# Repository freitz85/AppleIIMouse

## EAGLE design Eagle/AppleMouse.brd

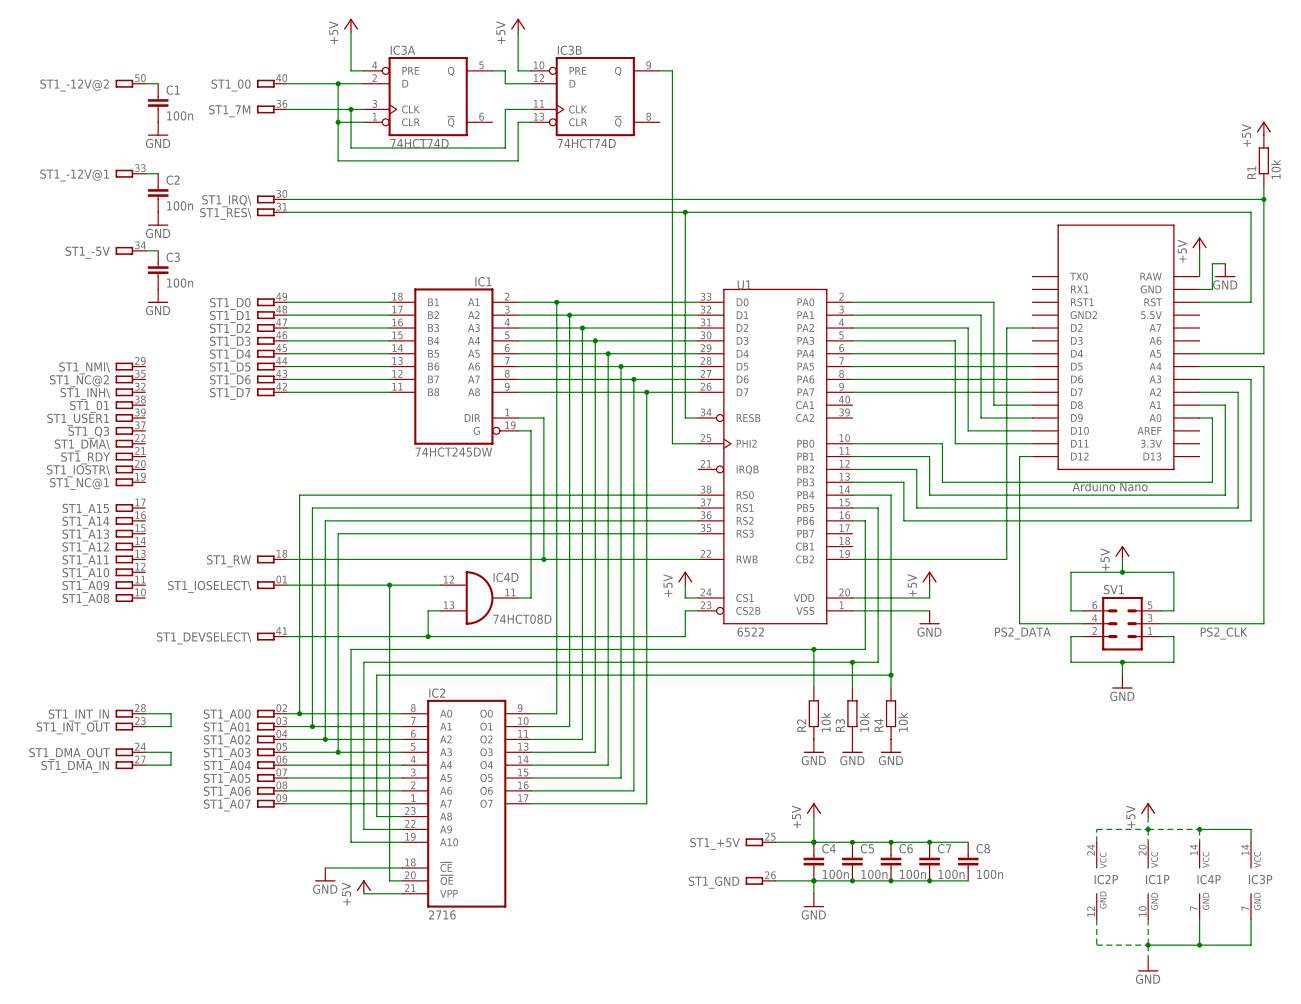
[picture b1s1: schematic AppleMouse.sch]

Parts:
C1, C2, C3, C4, C5, C6, C7, C8: 100n; C0805
IC1: 74HCT245DW; SO20W
IC2: 2716; DIL24
IC3: 74HCT74D; SO14
IC4: 74HCT08D; SO14
R1, R2, R3, R4: 10k; R0805
ST1: A2-50PINSLOT1-3; A2-50PIN-SL1-3
SV1: ML6
U1: 6522; DIP40
U$1: NANO

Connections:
+5V: C4.1, C5.1, C6.1, C7.1, C8.1, IC1.20 (VCC), IC2.21 (VPP), IC2.24 (VCC), IC3.4 (PRE), IC3.10 (PRE), IC3.14 (VCC), IC4.14 (VCC), R1.2, ST1.25, SV1.5, SV1.6, U1.20 (VDD), U1.24 (CS1), U$1.RAW
GND: C1.2, C2.2, C3.2, C4.2, C5.2, C6.2, C7.2, C8.2, IC1.10 (GND), IC2.12 (GND), IC2.18 (!CE), IC3.7 (GND), IC4.7 (GND), R2.1, R3.1, R4.1, ST1.26, SV1.1, SV1.2, U1.1 (VSS), U$1.GND
unnamed: IC1.18 (B1), ST1.49
unnamed: IC1.17 (B2), ST1.48
unnamed: IC1.16 (B3), ST1.47
unnamed: IC1.15 (B4), ST1.46
unnamed: IC1.14 (B5), ST1.45
unnamed: IC1.13 (B6), ST1.44
unnamed: IC1.12 (B7), ST1.43
unnamed: IC1.11 (B8), ST1.42
unnamed: IC1.5 (A4), IC2.13 (O3), U1.30 (D3)
unnamed: IC1.4 (A3), IC2.11 (O2), U1.31 (D2)
unnamed: IC1.3 (A2), IC2.10 (O1), U1.32 (D1)
unnamed: IC1.2 (A1), IC2.9 (O0), U1.33 (D0)
unnamed: IC1.9 (A8), IC2.17 (O7), U1.26 (D7)
unnamed: IC1.7 (A6), IC2.15 (O5), U1.28 (D5)
unnamed: IC1.8 (A7), IC2.16 (O6), U1.27 (D6)
unnamed: R1.1, ST1.30, U$1.A5
unnamed: ST1.31, U1.34 (RESB), U$1.RST
unnamed: U1.13 (PB3), U$1.A3
unnamed: IC2.20 (!OE), IC4.12 (I0), ST1.01
unnamed: U1.10 (PB0), U$1.A0
unnamed: IC2.7 (A1), ST1.03, U1.37 (RS1)
unnamed: U1.12 (PB2), U$1.A2
unnamed: IC2.5 (A3), ST1.05, U1.35 (RS3)
unnamed: IC2.4 (A4), ST1.06
unnamed: IC2.3 (A5), ST1.07
unnamed: IC2.2 (A6), ST1.08
unnamed: IC2.1 (A7), ST1.09
unnamed: IC1.1 (DIR), ST1.18, U1.22 (RWB)
unnamed: C1.1, ST1.50
unnamed: C2.1, ST1.33
unnamed: ST1.24, ST1.27
unnamed: ST1.23, ST1.28
unnamed: C3.1, ST1.34
unnamed: U1.19 (CB2), U$1.D2
unnamed: IC2.8 (A0), ST1.02, U1.38 (RS0)
unnamed: U1.11 (PB1), U$1.A1
unnamed: IC4.13 (I1), ST1.41, U1.23 (CS2B)
unnamed: IC2.6 (A2), ST1.04, U1.36 (RS2)
unnamed: IC1.6 (A5), IC2.14 (O4), U1.29 (D4)
unnamed: U1.3 (PA1), U$1.D9
unnamed: U1.2 (PA0), U$1.D8
unnamed: U1.4 (PA2), U$1.D10
unnamed: U1.5 (PA3), U$1.D11
unnamed: U1.6 (PA4), U$1.D4
unnamed: U1.7 (PA5), U$1.D5
unnamed: U1.8 (PA6), U$1.D6
unnamed: U1.9 (PA7), U$1.D7
unnamed: IC3.9 (Q), U1.25 (PHI2)
unnamed: IC2.23 (A8), R4.2, U1.14 (PB4)
unnamed: IC2.22 (A9), R3.2, U1.15 (PB5)
unnamed: IC2.19 (A10), R2.2, U1.16 (PB6)
unnamed: IC1.19 (G), IC4.11 (O)
unnamed: IC3.5 (Q), IC3.12 (D)
unnamed: IC3.1 (CLR), IC3.2 (D), IC3.13 (CLR), ST1.40
unnamed: IC3.3 (CLK), IC3.11 (CLK), ST1.36
PS2_CLK: SV1.3, U$1.A4
PS2_DATA: SV1.4, U$1.D12

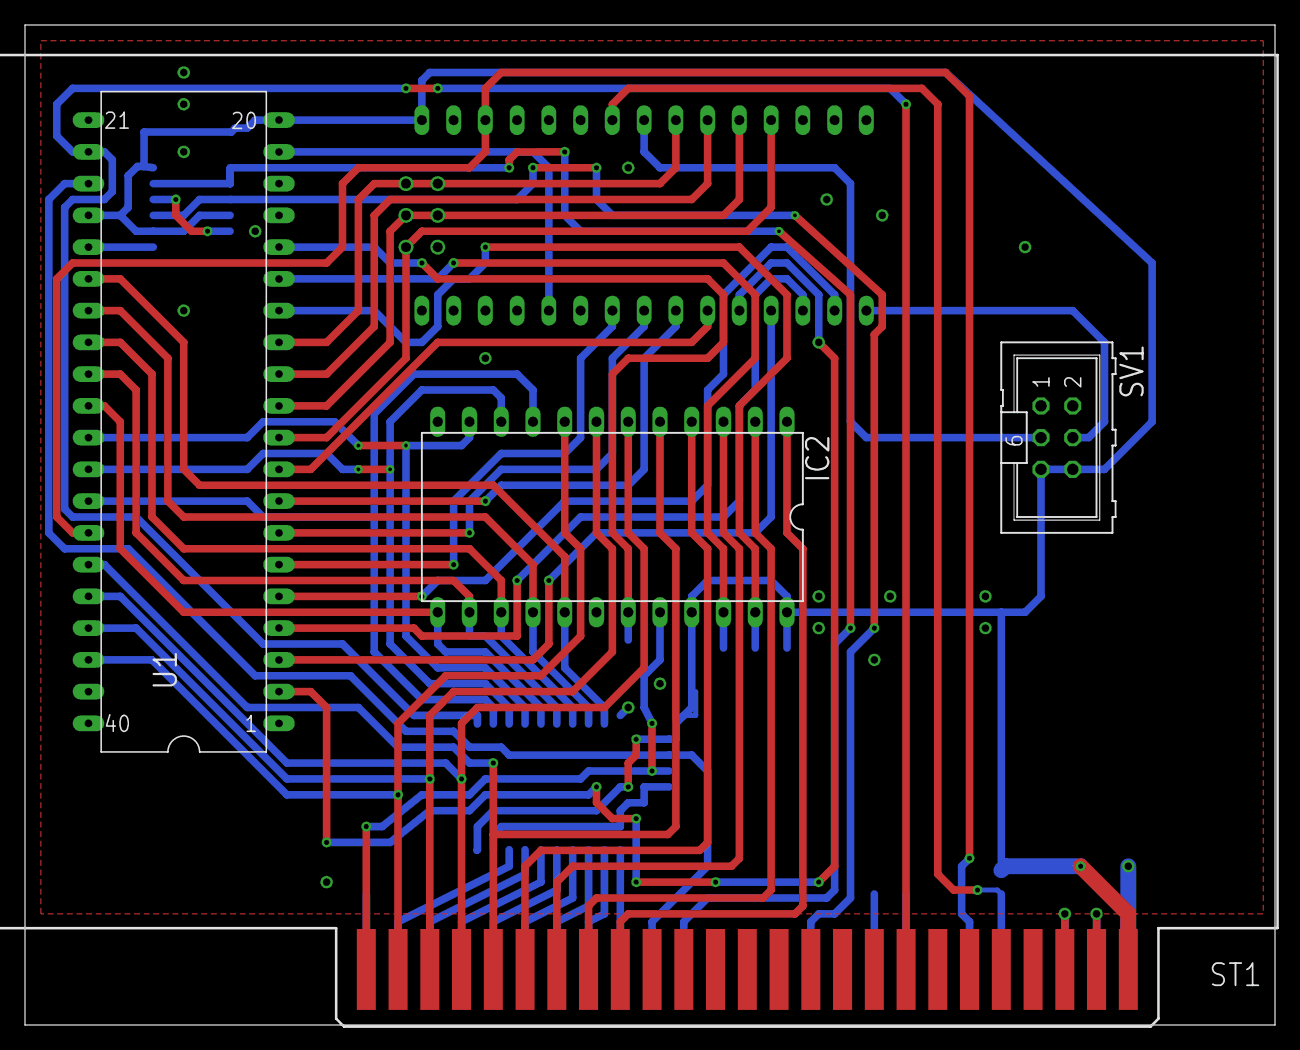
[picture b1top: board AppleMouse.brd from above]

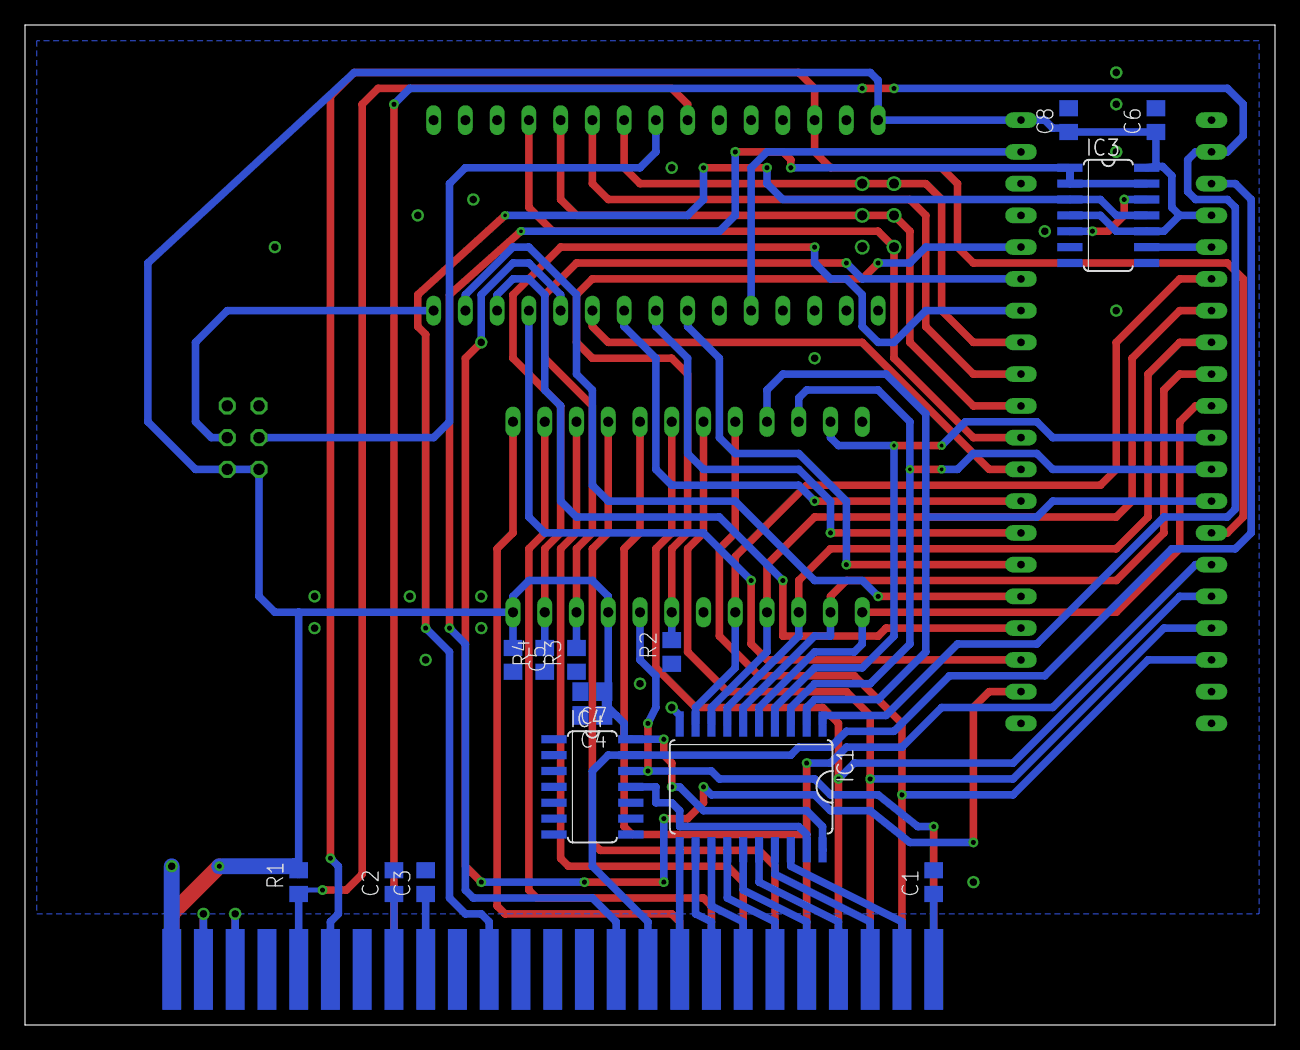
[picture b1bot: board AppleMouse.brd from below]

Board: 2 copper layers, 100.0 x 80.0 mm, 20 parts (15 on the bottom side), 59 nets.

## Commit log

2019-05-27 A little disassembly
2019-06-17 Mouse ctrl and top added
